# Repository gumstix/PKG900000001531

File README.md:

# Gumstix Raspberry Pi CM4 + Pixhawk FMUv6
## PKG900000001531 ![][thumbnail]

The **Gumstix Raspberry Pi CM4 + Pixhawk FMUv6** brings together 3 powerful compute devices.  With the Raspberry Pi CM4 module, the Google Coral TPU, and the ST Micro STM32F7 MCU, along with support hardware for MAVs, rovers and other robotics platforms,  designing TensorFlow-assisted autonomous vehicles has never been so accessible.

The *CM4 + Pixhawk FMUv6* is one of the first boards conforming to Pixhawk's v6 specification for Flight Management Units (FMUs), including on-board sensor bank, standard Pixhawk data and power connectors, octal PWM outputs, and firmware support.

The *CM4 + Pixhawk FMUv6* features single-connection programming and debugging.  Power the PCB, flash the CM4's MMC, program the FMU's frimware, or monitor their serial consoles from the same USB Type-C connection.

__Features Include__:
* Raspberry Pi CM4 connector
* Dual Raspberry Pi Camera connectors
* Serial console over USB
* USB Type-C power delivery
* STMicro STM32H753 MCU
* Pixhawk GPS, analog power, RC, and CAN connectors
* 8 PWM outputs
* On-board accelerometer, magnetometer and gyroscope
* On-board barometer
* ASMedia ASM1142 PCIe to USB3.1 controller
* Google Coral G313 TPU (via USB3)

__Links:__
* [AutoDoc Datasheet][autodoc]
* [Specifications][spec]
* [Store Page][store]
* [Schematics and Layout][hardware]

[thumbnail]: about:blank
[autodoc]: PKG900000001531_AutoDoc.pdf
[spec]: PKG900000001531_SpecSheet.pdf
[store]: https://store.gumstix.com/cm4-pixhawk6-mini/
[hardware]: hardware/hardware.md
[firmware]: firmware/firmware.md

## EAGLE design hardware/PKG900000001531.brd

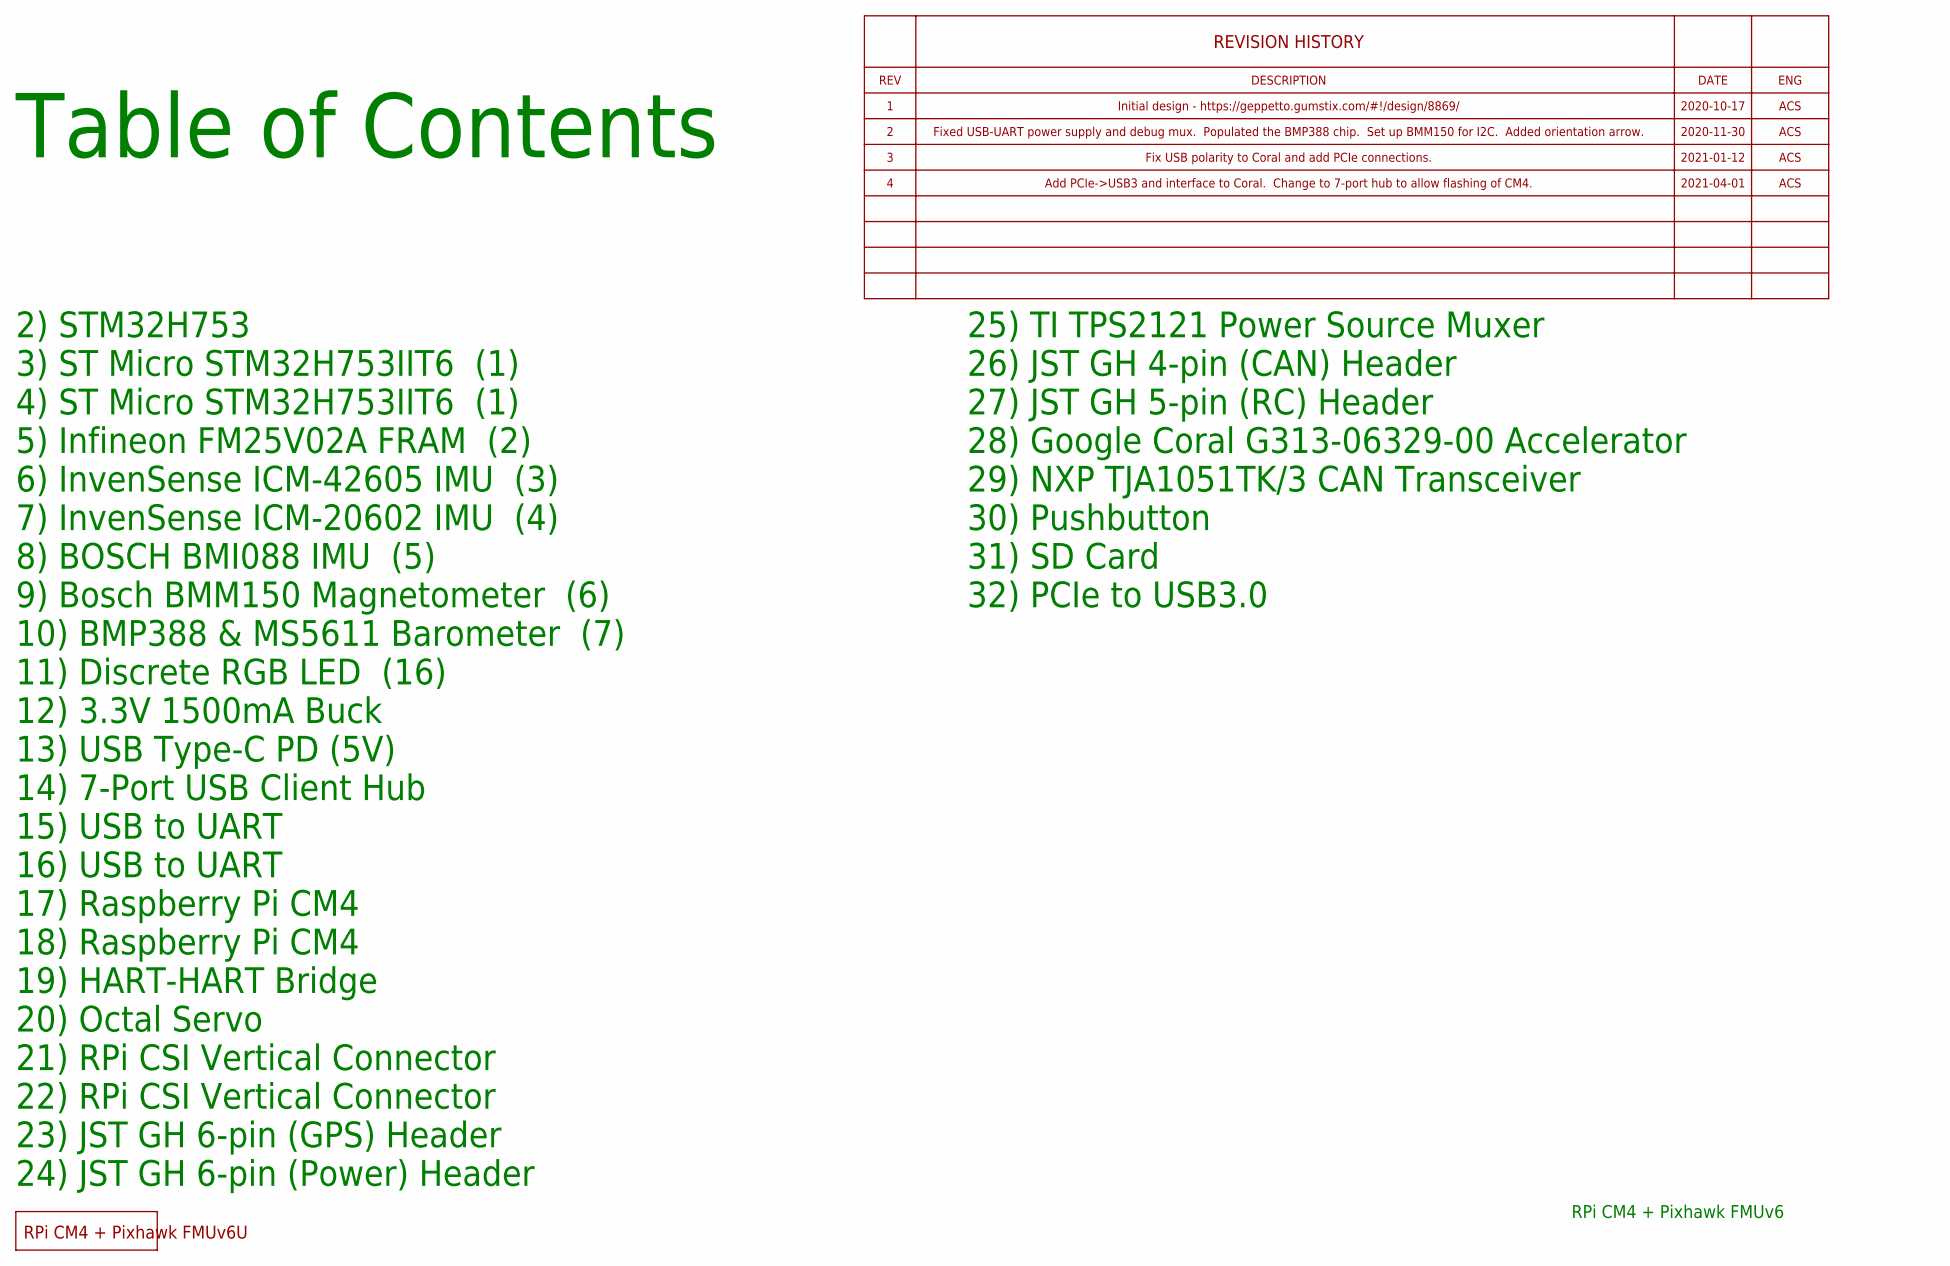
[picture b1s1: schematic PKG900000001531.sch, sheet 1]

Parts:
FD1, FD2, FD3, FD4, FD5, FD6, FD7, FD8: DNP; FIDUCIAL
U$2: DNP; UPVERTER_LABEL_SMALL

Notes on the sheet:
Table of Contents
RPi CM4 + Pixhawk FMUv6
2) STM32H753
3) ST Micro STM32H753IIT6 (1)
4) ST Micro STM32H753IIT6 (1)
5) Infineon FM25V02A FRAM (2)
6) InvenSense ICM-42605 IMU (3)
7) InvenSense ICM-20602 IMU (4)
8) BOSCH BMI088 IMU (5)
9) Bosch BMM150 Magnetometer (6)
10) BMP388 & MS5611 Barometer (7)
11) Discrete RGB LED (16)
12) 3.3V 1500mA Buck
13) USB Type-C PD (5V)
14) 7-Port USB Client Hub
15) USB to UART
16) USB to UART
17) Raspberry Pi CM4
18) Raspberry Pi CM4
19) HART-HART Bridge
20) Octal Servo
21) RPi CSI Vertical Connector
22) RPi CSI Vertical Connector
23) JST GH 6-pin (GPS) Header
24) JST GH 6-pin (Power) Header
25) TI TPS2121 Power Source Muxer
26) JST GH 4-pin (CAN) Header
27) JST GH 5-pin (RC) Header
28) Google Coral G313-06329-00 Accelerator
29) NXP TJA1051TK/3 CAN Transceiver
30) Pushbutton
31) SD Card
32) PCIe to USB3.0
Initial design - https://geppetto.gumstix.com/#\!/design/8869/
2020-10-17
ACS
2020-11-30
Fixed USB-UART power supply and debug mux. Populated the BMP388 chip. Set up BMM150 for I2C. Added orientation arrow.
Fix USB polarity to Coral and add PCIe connections.
2021-01-12

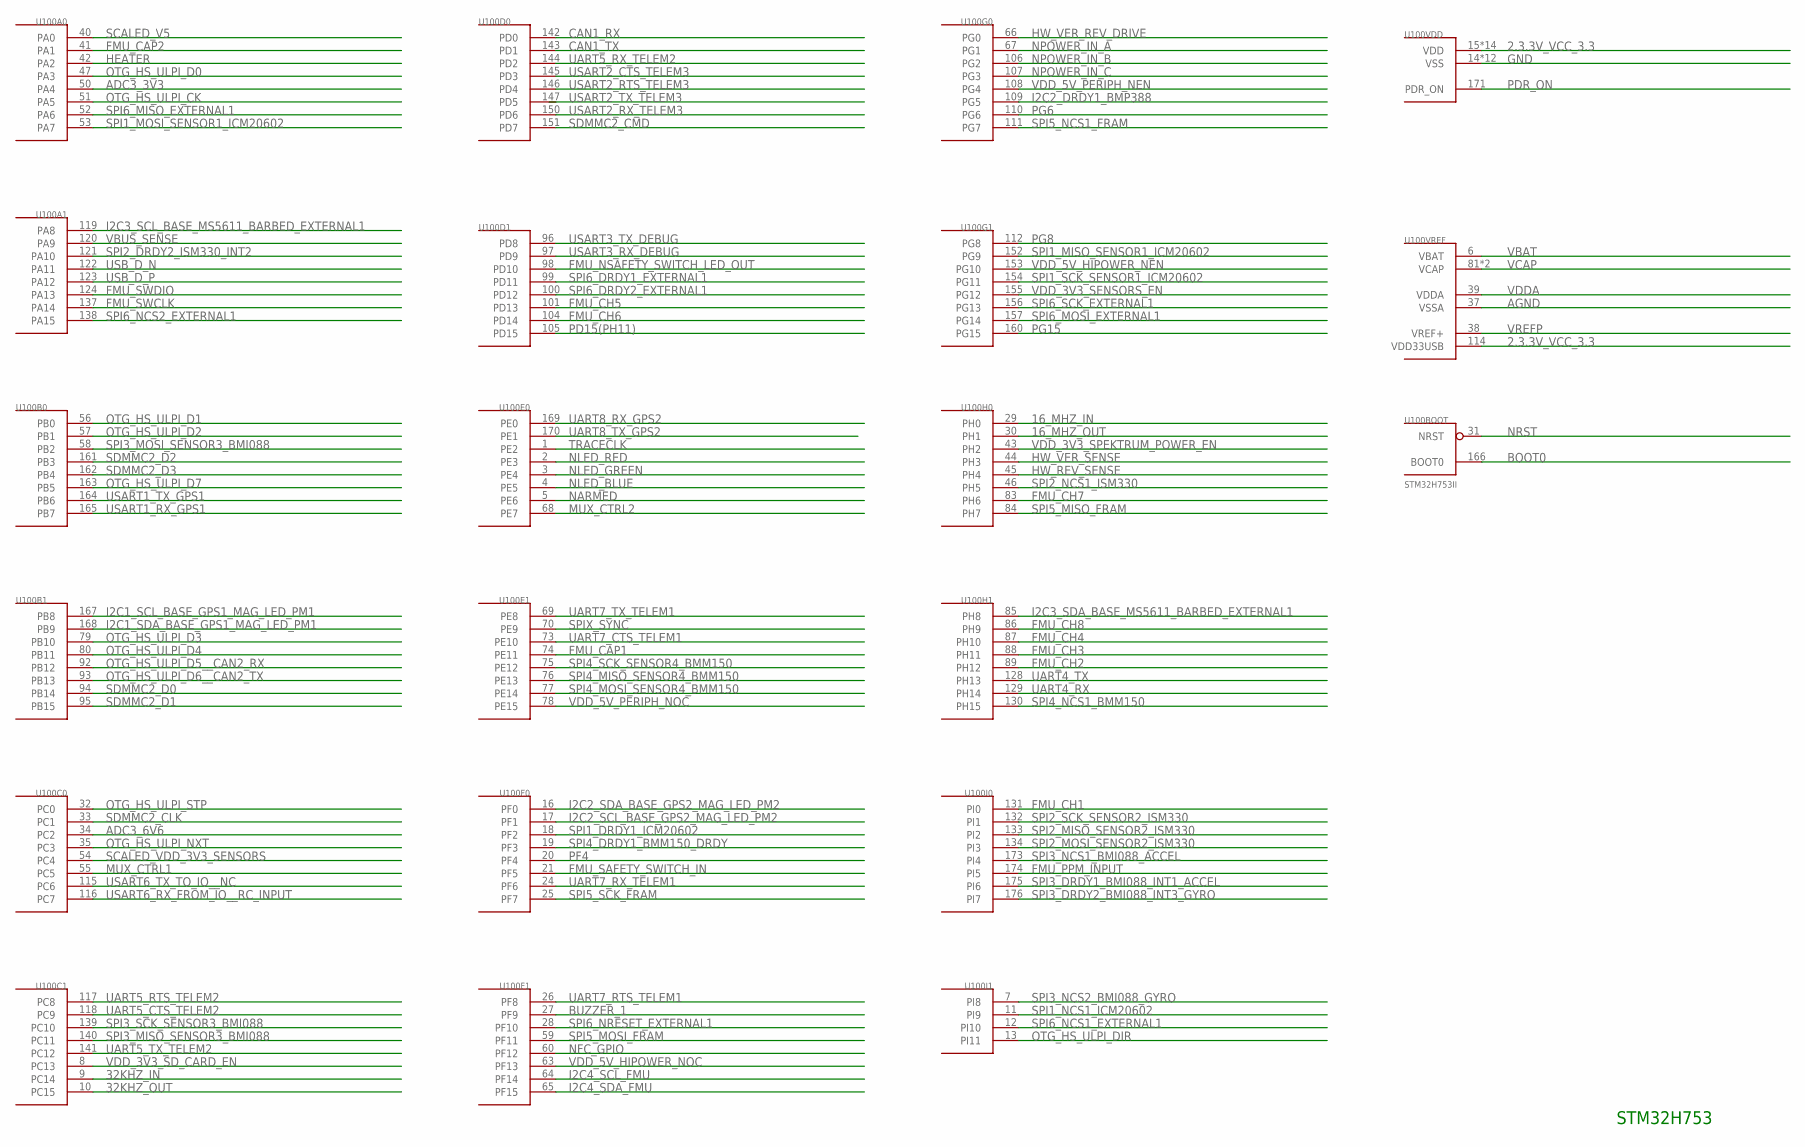
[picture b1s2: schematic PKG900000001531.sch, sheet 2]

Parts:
U100: STM32H753II; LQFP176

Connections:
2.3.3V_VCC_3.3: U100.15 (VDD), U100.23 (VDD), U100.36 (VDD), U100.49 (VDD), U100.62 (VDD), U100.72 (VDD), U100.82 (VDD), U100.91 (VDD), U100.103 (VDD), U100.114 (VDD33USB), U100.127 (VDD), U100.136 (VDD), U100.149 (VDD), U100.159 (VDD), U100.172 (VDD); also elsewhere on the board
16_MHZ_IN: U100.29 (PH0); also elsewhere on the board
16_MHZ_OUT: U100.30 (PH1); also elsewhere on the board
32KHZ_IN: U100.9 (PC14); also elsewhere on the board
32KHZ_OUT: U100.10 (PC15); also elsewhere on the board
ADC3_3V3: U100.50 (PA4); also elsewhere on the board
ADC3_6V6: U100.34 (PC2); also elsewhere on the board
AGND: U100.37 (VSSA); also elsewhere on the board
BOOT0: U100.166 (BOOT0); also elsewhere on the board
BUZZER_1: U100.27 (PF9)
CAN1_RX: U100.142 (PD0); also elsewhere on the board
CAN1_TX: U100.143 (PD1); also elsewhere on the board
FMU_CAP1: U100.74 (PE11)
FMU_CAP2: U100.41 (PA1)
FMU_CH1: U100.131 (PI0); also elsewhere on the board
FMU_CH2: U100.89 (PH12); also elsewhere on the board
FMU_CH3: U100.88 (PH11); also elsewhere on the board
FMU_CH4: U100.87 (PH10); also elsewhere on the board
FMU_CH5: U100.101 (PD13); also elsewhere on the board
FMU_CH6: U100.104 (PD14); also elsewhere on the board
FMU_CH7: U100.83 (PH6); also elsewhere on the board
FMU_CH8: U100.86 (PH9); also elsewhere on the board
FMU_NSAFETY_SWITCH_LED_OUT: U100.98 (PD10)
FMU_PPM_INPUT: U100.174 (PI5); also elsewhere on the board
FMU_SAFETY_SWITCH_IN: U100.21 (PF5)
FMU_SWCLK: U100.137 (PA14); also elsewhere on the board
FMU_SWDIO: U100.124 (PA13); also elsewhere on the board
GND: U100.14 (VSS), U100.22 (VSS), U100.48 (VSS), U100.61 (VSS), U100.71 (VSS), U100.90 (VSS), U100.102 (VSS), U100.113 (VSS), U100.126 (VSS), U100.135 (VSS), U100.148 (VSS), U100.158 (VSS); also elsewhere on the board
HEATER: U100.42 (PA2)
HW_REV_SENSE: U100.45 (PH4); also elsewhere on the board
HW_VER_REV_DRIVE: U100.66 (PG0); also elsewhere on the board
HW_VER_SENSE: U100.44 (PH3); also elsewhere on the board
I2C1_SCL_BASE_GPS1_MAG_LED_PM1: U100.167 (PB8); also elsewhere on the board
I2C1_SDA_BASE_GPS1_MAG_LED_PM1: U100.168 (PB9); also elsewhere on the board
I2C2_DRDY1_BMP388: U100.109 (PG5); also elsewhere on the board
I2C2_SCL_BASE_GPS2_MAG_LED_PM2: U100.17 (PF1)
I2C2_SDA_BASE_GPS2_MAG_LED_PM2: U100.16 (PF0)
I2C3_SCL_BASE_MS5611_BARBED_EXTERNAL1: U100.119 (PA8); also elsewhere on the board
I2C3_SDA_BASE_MS5611_BARBED_EXTERNAL1: U100.85 (PH8); also elsewhere on the board
I2C4_SCL_FMU: U100.64 (PF14); also elsewhere on the board
I2C4_SDA_FMU: U100.65 (PF15); also elsewhere on the board
MUX_CTRL1: U100.55 (PC5)
MUX_CTRL2: U100.68 (PE7)
NARMED: U100.5 (PE6)
NFC_GPIO: U100.60 (PF12); also elsewhere on the board
NLED_BLUE: U100.4 (PE5); also elsewhere on the board
NLED_GREEN: U100.3 (PE4); also elsewhere on the board
NLED_RED: U100.2 (PE3); also elsewhere on the board
NPOWER_IN_A: U100.67 (PG1)
NPOWER_IN_B: U100.106 (PG2)
NPOWER_IN_C: U100.107 (PG3)
NRST: U100.31 (NRST); also elsewhere on the board
OTG_HS_ULPI_CK: U100.51 (PA5); also elsewhere on the board
OTG_HS_ULPI_D0: U100.47 (PA3); also elsewhere on the board
OTG_HS_ULPI_D1: U100.56 (PB0); also elsewhere on the board
OTG_HS_ULPI_D2: U100.57 (PB1); also elsewhere on the board
OTG_HS_ULPI_D3: U100.79 (PB10); also elsewhere on the board
OTG_HS_ULPI_D4: U100.80 (PB11); also elsewhere on the board
OTG_HS_ULPI_D5__CAN2_RX: U100.92 (PB12); also elsewhere on the board
OTG_HS_ULPI_D6__CAN2_TX: U100.93 (PB13); also elsewhere on the board
OTG_HS_ULPI_D7: U100.163 (PB5); also elsewhere on the board
OTG_HS_ULPI_DIR: U100.13 (PI11); also elsewhere on the board
OTG_HS_ULPI_NXT: U100.35 (PC3); also elsewhere on the board
OTG_HS_ULPI_STP: U100.32 (PC0); also elsewhere on the board
PD15(PH11): U100.105 (PD15); also elsewhere on the board
PDR_ON: U100.171 (PDR_ON); also elsewhere on the board
PF4: U100.20 (PF4)
PG6: U100.110 (PG6)
PG8: U100.112 (PG8)
PG15: U100.160 (PG15)
SCALED_V5: U100.40 (PA0); also elsewhere on the board
SCALED_VDD_3V3_SENSORS: U100.54 (PC4); also elsewhere on the board
SDMMC2_CLK: U100.33 (PC1); also elsewhere on the board
SDMMC2_CMD: U100.151 (PD7); also elsewhere on the board
SDMMC2_D0: U100.94 (PB14); also elsewhere on the board
SDMMC2_D1: U100.95 (PB15); also elsewhere on the board
SDMMC2_D2: U100.161 (PB3); also elsewhere on the board
SDMMC2_D3: U100.162 (PB4); also elsewhere on the board
SPI1_DRDY1_ICM20602: U100.18 (PF2); also elsewhere on the board
SPI1_MISO_SENSOR1_ICM20602: U100.152 (PG9); also elsewhere on the board
SPI1_MOSI_SENSOR1_ICM20602: U100.53 (PA7); also elsewhere on the board
SPI1_NCS1_ICM20602: U100.11 (PI9); also elsewhere on the board
SPI1_SCK_SENSOR1_ICM20602: U100.154 (PG11); also elsewhere on the board
SPI2_DRDY2_ISM330_INT2: U100.121 (PA10); also elsewhere on the board
SPI2_MISO_SENSOR2_ISM330: U100.133 (PI2); also elsewhere on the board
SPI2_MOSI_SENSOR2_ISM330: U100.134 (PI3); also elsewhere on the board
SPI2_NCS1_ISM330: U100.46 (PH5); also elsewhere on the board
SPI2_SCK_SENSOR2_ISM330: U100.132 (PI1); also elsewhere on the board
SPI3_DRDY1_BMI088_INT1_ACCEL: U100.175 (PI6); also elsewhere on the board
SPI3_DRDY2_BMI088_INT3_GYRO: U100.176 (PI7); also elsewhere on the board
SPI3_MISO_SENSOR3_BMI088: U100.140 (PC11); also elsewhere on the board
SPI3_MOSI_SENSOR3_BMI088: U100.58 (PB2); also elsewhere on the board
SPI3_NCS1_BMI088_ACCEL: U100.173 (PI4); also elsewhere on the board
SPI3_NCS2_BMI088_GYRO: U100.7 (PI8); also elsewhere on the board
SPI3_SCK_SENSOR3_BMI088: U100.139 (PC10); also elsewhere on the board
SPI4_DRDY1_BMM150_DRDY: U100.19 (PF3); also elsewhere on the board
SPI4_MISO_SENSOR4_BMM150: U100.76 (PE13); also elsewhere on the board
SPI4_MOSI_SENSOR4_BMM150: U100.77 (PE14); also elsewhere on the board
SPI4_NCS1_BMM150: U100.130 (PH15); also elsewhere on the board
SPI4_SCK_SENSOR4_BMM150: U100.75 (PE12); also elsewhere on the board
SPI5_MISO_FRAM: U100.84 (PH7); also elsewhere on the board
SPI5_MOSI_FRAM: U100.59 (PF11); also elsewhere on the board
SPI5_NCS1_FRAM: U100.111 (PG7); also elsewhere on the board
SPI5_SCK_FRAM: U100.25 (PF7); also elsewhere on the board
SPI6_DRDY1_EXTERNAL1: U100.99 (PD11)
SPI6_DRDY2_EXTERNAL1: U100.100 (PD12)
SPI6_MISO_EXTERNAL1: U100.52 (PA6)
SPI6_MOSI_EXTERNAL1: U100.157 (PG14)
SPI6_NCS1_EXTERNAL1: U100.12 (PI10)
SPI6_NCS2_EXTERNAL1: U100.138 (PA15)
SPI6_NRESET_EXTERNAL1: U100.28 (PF10)
SPI6_SCK_EXTERNAL1: U100.156 (PG13); also elsewhere on the board
SPIX_SYNC: U100.70 (PE9)
TRACECLK: U100.1 (PE2)
UART4_RX: U100.129 (PH14)
UART4_TX: U100.128 (PH13)
UART5_CTS_TELEM2: U100.118 (PC9); also elsewhere on the board
UART5_RTS_TELEM2: U100.117 (PC8); also elsewhere on the board
UART5_RX_TELEM2: U100.144 (PD2); also elsewhere on the board
UART5_TX_TELEM2: U100.141 (PC12); also elsewhere on the board
UART7_CTS_TELEM1: U100.73 (PE10)
UART7_RTS_TELEM1: U100.26 (PF8)
UART7_RX_TELEM1: U100.24 (PF6)
UART7_TX_TELEM1: U100.69 (PE8)
UART8_RX_GPS2: U100.169 (PE0)
UART8_TX_GPS2: U100.170 (PE1)
USART1_RX_GPS1: U100.165 (PB7); also elsewhere on the board
USART1_TX_GPS1: U100.164 (PB6); also elsewhere on the board
USART2_CTS_TELEM3: U100.145 (PD3)
USART2_RTS_TELEM3: U100.146 (PD4)
USART2_RX_TELEM3: U100.150 (PD6)
USART3_RX_DEBUG: U100.97 (PD9); also elsewhere on the board
USART3_TX_DEBUG: U100.96 (PD8); also elsewhere on the board
USART6_RX_FROM_IO__RC_INPUT: U100.116 (PC7); also elsewhere on the board
USART6_TX_TO_IO__NC: U100.115 (PC6)
USB_D_N: U100.122 (PA11); also elsewhere on the board
USB_D_P: U100.123 (PA12); also elsewhere on the board
VBAT: U100.6 (VBAT); also elsewhere on the board
VBUS_SENSE: U100.120 (PA9); also elsewhere on the board
VCAP: U100.81 (VCAP), U100.125 (VCAP); also elsewhere on the board
VDDA: U100.39 (VDDA); also elsewhere on the board
VDD_3V3_SD_CARD_EN: U100.8 (PC13); also elsewhere on the board
VDD_3V3_SENSORS_EN: U100.155 (PG12); also elsewhere on the board
VDD_3V3_SPEKTRUM_POWER_EN: U100.43 (PH2); also elsewhere on the board
VDD_5V_HIPOWER_NEN: U100.153 (PG10); also elsewhere on the board
VDD_5V_HIPOWER_NOC: U100.63 (PF13); also elsewhere on the board
VDD_5V_PERIPH_NEN: U100.108 (PG4); also elsewhere on the board
VDD_5V_PERIPH_NOC: U100.78 (PE15); also elsewhere on the board
VREFP: U100.38 (VREF+); also elsewhere on the board

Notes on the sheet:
STM32H753

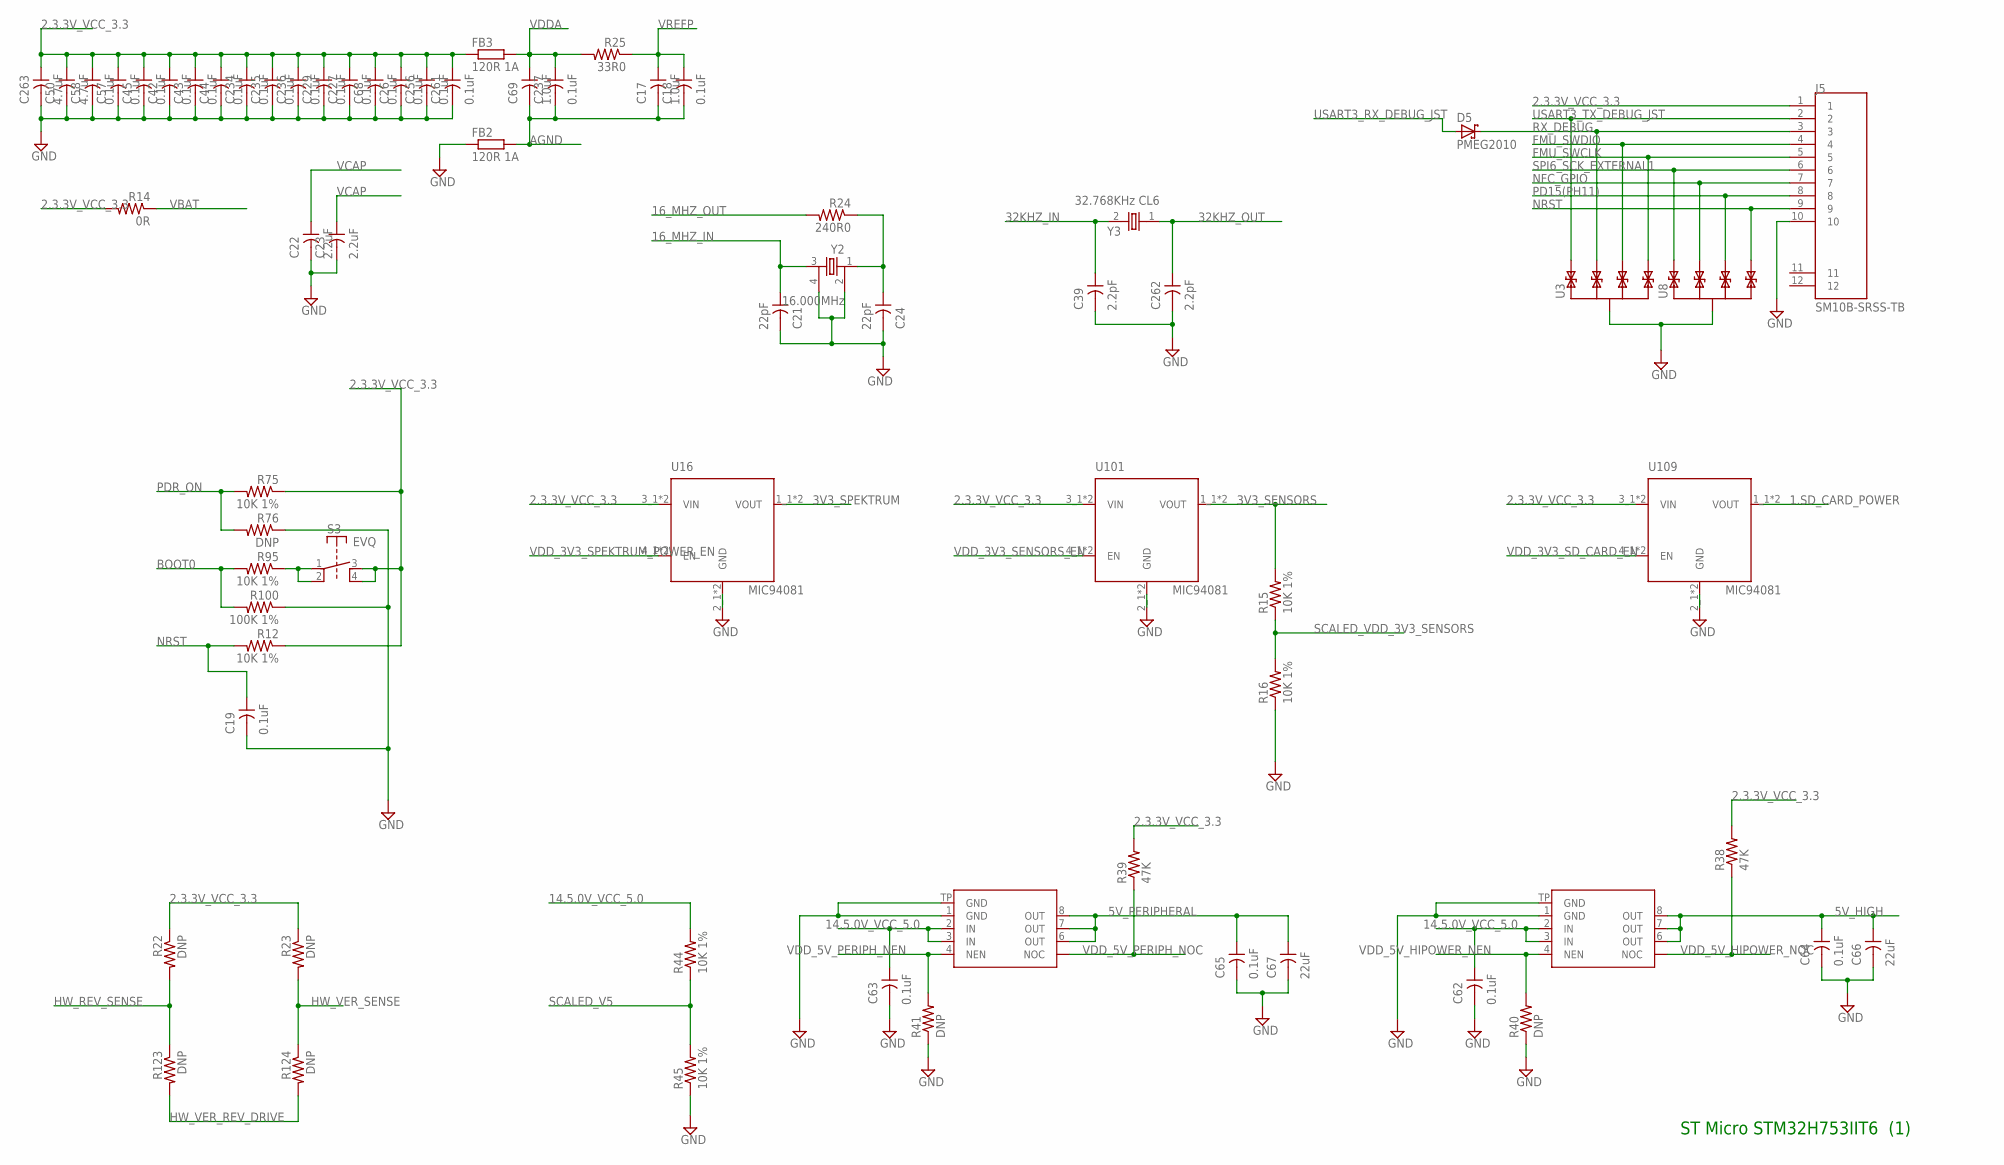
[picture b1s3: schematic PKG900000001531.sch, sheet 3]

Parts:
C17, C69: 1.0uF; 0402
C18, C19, C26, C42, C43, C44, C45, C57, C58, C62, C63, C64, C65, C68, C227, C229, C234, C235, C236, C237, C256, C261: 0.1uF; 0201
C21, C24: 22pF; 0201
C22, C23: 2.2uF; 0603
C39, C262: 2.2pF; 0201
C50, C263: 4.7uF; 0603
C66, C67: 22uF; 0805
D5: PMEG2010; SOD123F
FB2, FB3: 120R 1A; 0402
J5: SM10B-SRSS-TB
R12, R15, R16, R44, R45, R75, R95: 10K 1%; 0201
R14: 0R; 0402
R22, R23, R40, R41, R76, R123, R124: DNP; 0201
R24: 240R0; 0201
R25: 33R0; 0201
R38, R39: 47K; 0201
R100: 100K 1%; 0201
S3: EVQ; KMT0
U1, U25: TPS2041BDGN; MSOP8-PAD
U3, U8: TPD4E02B0410-USON; UFDFN-10
U16, U101, U109: MIC94081; FTDFN-4
Y2: 16.000MHz; CRYSTAL-3225
Y3: 32.768KHz CL6; 1206

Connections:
1.SD_CARD_POWER: U109.1_1 (VOUT), U109.1_2 (VOUT); also elsewhere on the board
2.3.3V_VCC_3.3: C26.1, C42.1, C43.1, C44.1, C45.1, C50.1, C57.1, C58.1, C68.1, C227.1, C229.1, C234.1, C235.1, C236.1, C256.1, C261.1, C263.1, FB3.1, J5.1, R12.1, R14.2, R22.1, R23.1, R38.2, R39.2, R75.1, S3.3 (B), S3.4 (B'), U16.3_1 (VIN), U16.3_2 (VIN), U101.3_1 (VIN), U101.3_2 (VIN), U109.3_1 (VIN), U109.3_2 (VIN); also elsewhere on the board
3V3_SENSORS: R15.2, U101.1_1 (VOUT), U101.1_2 (VOUT); also elsewhere on the board
3V3_SPEKTRUM: U16.1_1 (VOUT), U16.1_2 (VOUT); also elsewhere on the board
5V_HIGH: C64.1, C66.1, U25.6 (OUT), U25.7 (OUT), U25.8 (OUT); also elsewhere on the board
5V_PERIPHERAL: C65.1, C67.1, U1.6 (OUT), U1.7 (OUT), U1.8 (OUT); also elsewhere on the board
14.5.0V_VCC_5.0: C62.1, C63.1, R44.2, U1.2 (IN), U1.3 (IN), U25.2 (IN), U25.3 (IN); also elsewhere on the board
16_MHZ_IN: C21.1, Y2.3; also elsewhere on the board
16_MHZ_OUT: R24.2; also elsewhere on the board
32KHZ_IN: C39.1, Y3.2; also elsewhere on the board
32KHZ_OUT: C262.1, Y3.1; also elsewhere on the board
AGND: C17.2, C18.2, C69.2, C237.2, FB2.2; also elsewhere on the board
BOOT0: R95.2, R100.2; also elsewhere on the board
BOOTBUT$1: R95.1, S3.1 (A), S3.2 (A')
FMU_SWCLK: J5.5, U3.5 (P4), U3.6 (P4); also elsewhere on the board
FMU_SWDIO: J5.4, U3.4 (P3), U3.7 (P3); also elsewhere on the board
GND: C19.2, C21.2, C22.2, C23.2, C24.2, C26.2, C39.2, C42.2, C43.2, C44.2, C45.2, C50.2, C57.2, C58.2, C62.2, C63.2, C64.2, C65.2, C66.2, C67.2, C68.2, C227.2, C229.2, C234.2, C235.2, C236.2, C256.2, C261.2, C262.2, C263.2, FB2.1, J5.10, R16.1, R40.1, R41.1, R45.1, R76.1, R100.1, U1.1 (GND), U1.TP (GND), U3.3 (SHIELD), U3.8 (SHIELD), U8.3 (SHIELD), U8.8 (SHIELD), U16.2_1 (GND), U16.2_2 (GND), U25.1 (GND), U25.TP (GND), U101.2_1 (GND), U101.2_2 (GND), U109.2_1 (GND), U109.2_2 (GND), Y2.2, Y2.4; also elsewhere on the board
HW_REV_SENSE: R22.2, R123.1; also elsewhere on the board
HW_VER_REV_DRIVE: R123.2, R124.2; also elsewhere on the board
HW_VER_SENSE: R23.2, R124.1; also elsewhere on the board
NFC_GPIO: J5.7, U8.2, U8.9 (P2); also elsewhere on the board
NRST: C19.1, J5.9, R12.2, U8.5 (P4), U8.6 (P4); also elsewhere on the board
PD15(PH11): J5.8, U8.4 (P3), U8.7 (P3); also elsewhere on the board
PDR_ON: R75.2, R76.2; also elsewhere on the board
RX_DEBUG: D5.C, J5.3, U3.2, U3.9 (P2)
SCALED_V5: R44.1, R45.2; also elsewhere on the board
SCALED_VDD_3V3_SENSORS: R15.1, R16.2; also elsewhere on the board
SPI6_SCK_EXTERNAL1: J5.6, U8.1, U8.10 (P1); also elsewhere on the board
STM_OSC2$1: C24.1, R24.1, Y2.1
USART3_RX_DEBUG_JST: D5.A; also elsewhere on the board
USART3_TX_DEBUG_JST: J5.2, U3.1, U3.10 (P1); also elsewhere on the board
VBAT: R14.1; also elsewhere on the board
VCAP: C22.1, C23.1; also elsewhere on the board
VDDA: C69.1, C237.1, FB3.2, R25.2; also elsewhere on the board
VDD_3V3_SD_CARD_EN: U109.4_1 (EN), U109.4_2 (EN); also elsewhere on the board
VDD_3V3_SENSORS_EN: U101.4_1 (EN), U101.4_2 (EN); also elsewhere on the board
VDD_3V3_SPEKTRUM_POWER_EN: U16.4_1 (EN), U16.4_2 (EN); also elsewhere on the board
VDD_5V_HIPOWER_NEN: R40.2, U25.4 (NEN); also elsewhere on the board
VDD_5V_HIPOWER_NOC: R38.1, U25.5 (NOC); also elsewhere on the board
VDD_5V_PERIPH_NEN: R41.2, U1.4 (NEN); also elsewhere on the board
VDD_5V_PERIPH_NOC: R39.1, U1.5 (NOC); also elsewhere on the board
VREFP: C17.1, C18.1, R25.1; also elsewhere on the board

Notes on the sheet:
ST Micro STM32H753IIT6 (1)

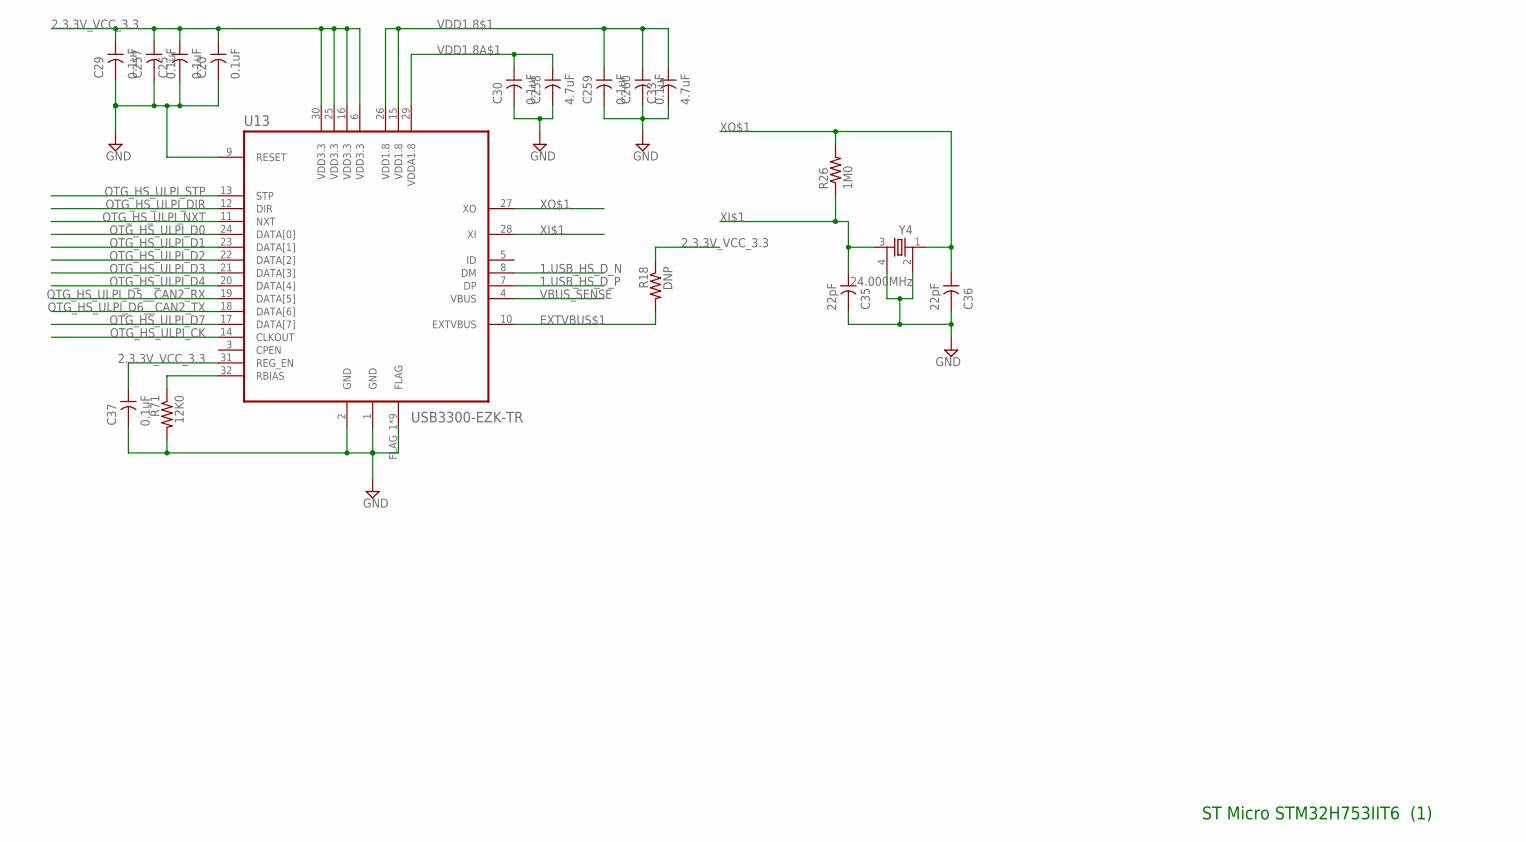
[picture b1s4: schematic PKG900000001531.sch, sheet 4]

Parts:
C20, C25, C29, C30, C37, C257, C259, C260: 0.1uF; 0201
C33, C258: 4.7uF; 0603
C35, C36: 22pF; 0201
R18: DNP; 0201
R26: 1M0; 0402
R71: 12K0; 0402
U13: USB3300-EZK-TR; QFN32-USB3300
Y4: 24.000MHz; CRYSTAL-3225

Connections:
1.USB_HS_D_N: U13.8 (DM); also elsewhere on the board
1.USB_HS_D_P: U13.7 (DP); also elsewhere on the board
2.3.3V_VCC_3.3: C20.1, C25.1, C29.1, C37.1, C257.1, R18.1, U13.6 (VDD3.3), U13.16 (VDD3.3), U13.25 (VDD3.3), U13.30 (VDD3.3), U13.31 (REG_EN); also elsewhere on the board
EXTVBUS$1: R18.2, U13.10 (EXTVBUS)
GND: C20.2, C25.2, C29.2, C30.2, C33.2, C35.2, C36.2, C37.2, C257.2, C258.2, C259.2, C260.2, R71.2, U13.1 (GND), U13.2 (GND), U13.9 (RESET), U13.FLAG_1 (FLAG), U13.FLAG_2 (FLAG), U13.FLAG_3 (FLAG), U13.FLAG_4 (FLAG), U13.FLAG_5 (FLAG), U13.FLAG_6 (FLAG), U13.FLAG_7 (FLAG), U13.FLAG_8 (FLAG), U13.FLAG_9 (FLAG), Y4.2, Y4.4; also elsewhere on the board
OTG_HS_ULPI_CK: U13.14 (CLKOUT); also elsewhere on the board
OTG_HS_ULPI_D0: U13.24 (DATA[0]); also elsewhere on the board
OTG_HS_ULPI_D1: U13.23 (DATA[1]); also elsewhere on the board
OTG_HS_ULPI_D2: U13.22 (DATA[2]); also elsewhere on the board
OTG_HS_ULPI_D3: U13.21 (DATA[3]); also elsewhere on the board
OTG_HS_ULPI_D4: U13.20 (DATA[4]); also elsewhere on the board
OTG_HS_ULPI_D5__CAN2_RX: U13.19 (DATA[5]); also elsewhere on the board
OTG_HS_ULPI_D6__CAN2_TX: U13.18 (DATA[6]); also elsewhere on the board
OTG_HS_ULPI_D7: U13.17 (DATA[7]); also elsewhere on the board
OTG_HS_ULPI_DIR: U13.12 (DIR); also elsewhere on the board
OTG_HS_ULPI_NXT: U13.11 (NXT); also elsewhere on the board
OTG_HS_ULPI_STP: U13.13 (STP); also elsewhere on the board
RBIAS$1: R71.1, U13.32 (RBIAS)
VBUS_SENSE: U13.4 (VBUS); also elsewhere on the board
VDD1.8$1: C33.1, C259.1, C260.1, U13.15 (VDD1.8), U13.26 (VDD1.8)
VDD1.8A$1: C30.1, C258.1, U13.29 (VDDA1.8)
XI$1: C35.1, R26.1, U13.28 (XI), Y4.3
XO$1: C36.1, R26.2, U13.27 (XO), Y4.1

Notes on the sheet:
ST Micro STM32H753IIT6 (1)

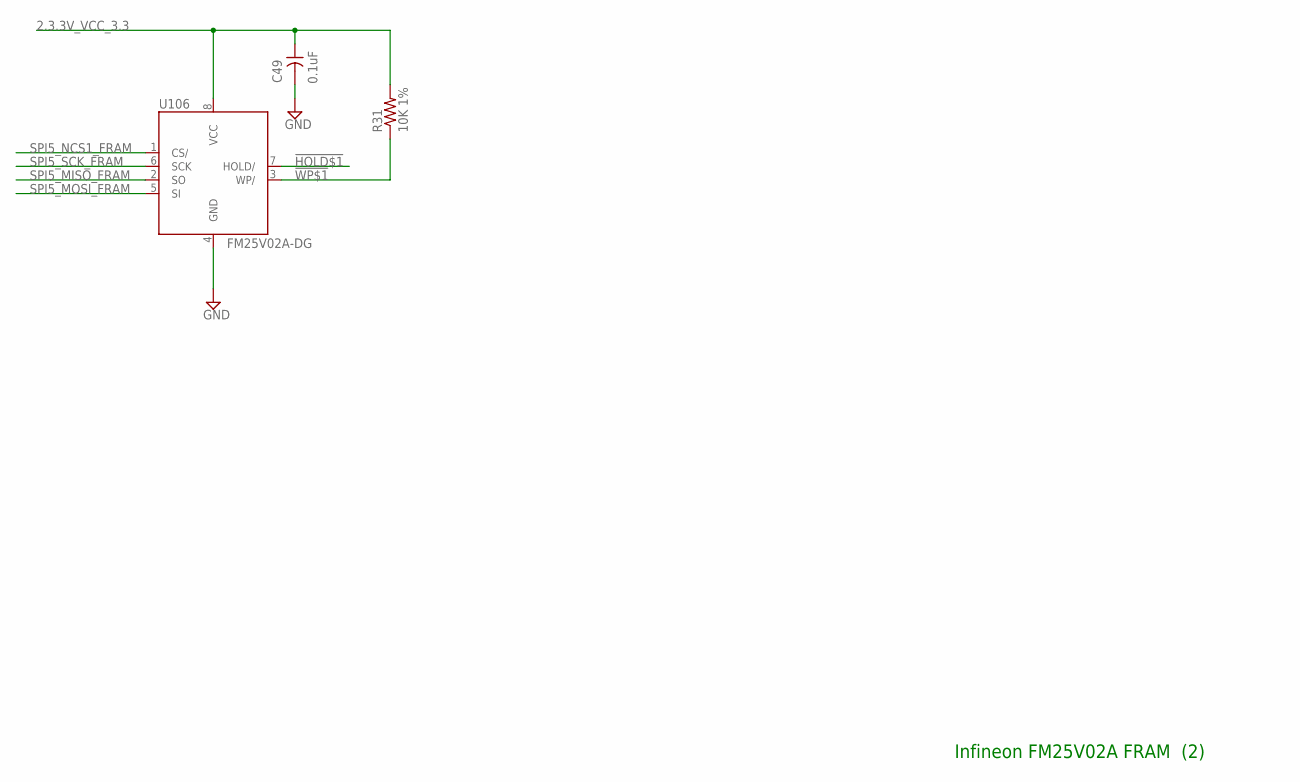
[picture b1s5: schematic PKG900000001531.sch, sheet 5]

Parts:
C49: 0.1uF; 0201
R31: 10K 1%; 0201
U106: FM25V02A-DG; DFN8-4X4.5

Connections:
2.3.3V_VCC_3.3: C49.1, R31.2, U106.8 (VCC); also elsewhere on the board
!HOLD$1: U106.7 (HOLD/)
!WP$1: R31.1, U106.3 (WP/)
GND: C49.2, U106.4 (GND); also elsewhere on the board
SPI5_MISO_FRAM: U106.2 (SO); also elsewhere on the board
SPI5_MOSI_FRAM: U106.5 (SI); also elsewhere on the board
SPI5_NCS1_FRAM: U106.1 (CS/); also elsewhere on the board
SPI5_SCK_FRAM: U106.6 (SCK); also elsewhere on the board

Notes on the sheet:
Infineon FM25V02A FRAM (2)

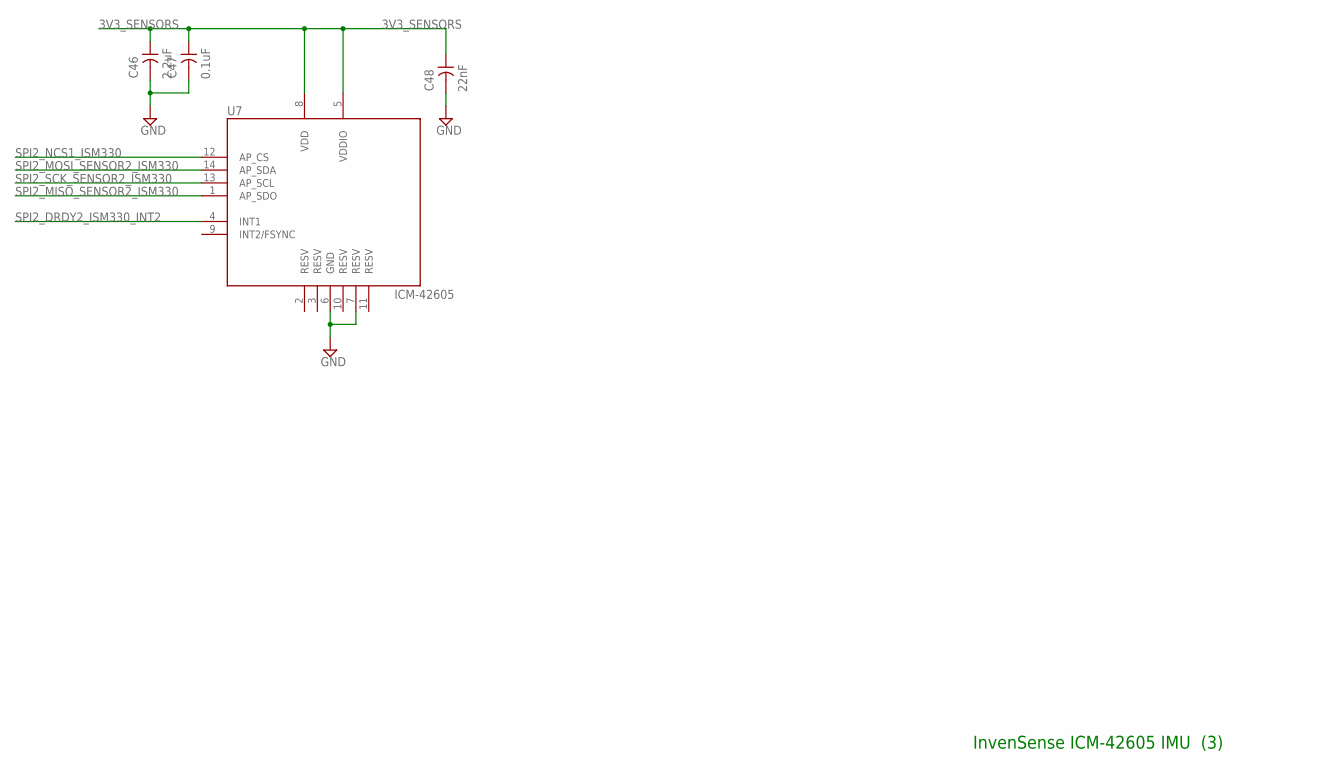
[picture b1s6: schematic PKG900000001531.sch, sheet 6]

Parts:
C46: 2.2uF; 0402
C47: 0.1uF; 0201
C48: 22nF; 0201
U7: ICM-42605; LGA14-2.5X3MM

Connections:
3V3_SENSORS: C46.1, C47.1, C48.1, U7.5 (VDDIO), U7.8 (VDD); also elsewhere on the board
GND: C46.2, C47.2, C48.2, U7.6 (GND), U7.7 (RESV); also elsewhere on the board
SPI2_DRDY2_ISM330_INT2: U7.4 (INT1); also elsewhere on the board
SPI2_MISO_SENSOR2_ISM330: U7.1 (AP_SDO); also elsewhere on the board
SPI2_MOSI_SENSOR2_ISM330: U7.14 (AP_SDA); also elsewhere on the board
SPI2_NCS1_ISM330: U7.12 (AP_CS); also elsewhere on the board
SPI2_SCK_SENSOR2_ISM330: U7.13 (AP_SCL); also elsewhere on the board

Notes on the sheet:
InvenSense ICM-42605 IMU (3)

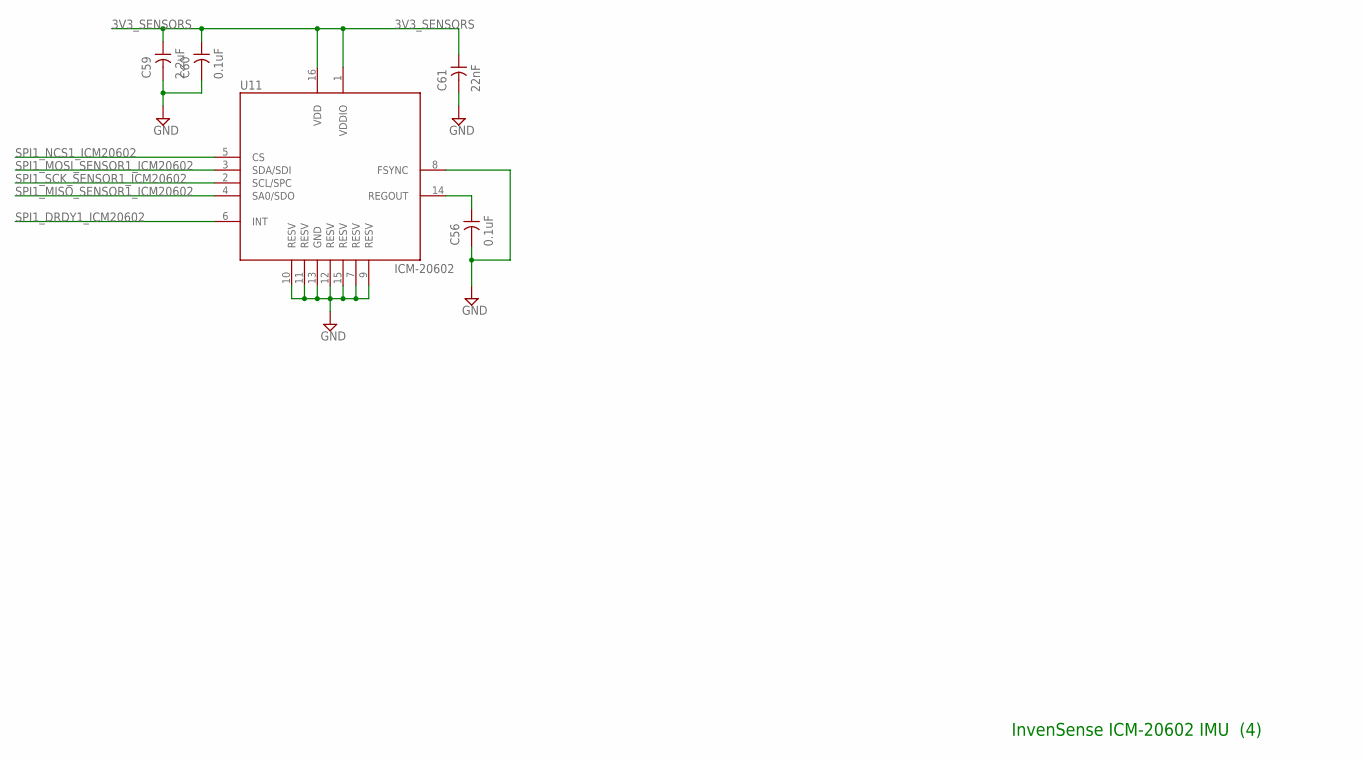
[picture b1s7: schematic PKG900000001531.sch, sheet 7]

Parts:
C56, C60: 0.1uF; 0201
C59: 2.2uF; 0402
C61: 22nF; 0201
U11: ICM-20602; LGA16-3X3MM

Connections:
3V3_SENSORS: C59.1, C60.1, C61.1, U11.1 (VDDIO), U11.16 (VDD); also elsewhere on the board
GND: C56.2, C59.2, C60.2, C61.2, U11.7 (RESV), U11.8 (FSYNC), U11.9 (RESV), U11.10 (RESV), U11.11 (RESV), U11.12 (RESV), U11.13 (GND), U11.15 (RESV); also elsewhere on the board
REGOUT$1: C56.1, U11.14 (REGOUT)
SPI1_DRDY1_ICM20602: U11.6 (INT); also elsewhere on the board
SPI1_MISO_SENSOR1_ICM20602: U11.4 (SA0/SDO); also elsewhere on the board
SPI1_MOSI_SENSOR1_ICM20602: U11.3 (SDA/SDI); also elsewhere on the board
SPI1_NCS1_ICM20602: U11.5 (CS); also elsewhere on the board
SPI1_SCK_SENSOR1_ICM20602: U11.2 (SCL/SPC); also elsewhere on the board

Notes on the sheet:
InvenSense ICM-20602 IMU (4)
